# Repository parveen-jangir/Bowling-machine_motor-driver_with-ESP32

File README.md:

# Bowling-machine_motor-driver_with-ESP32
In this project we develop both hardware and software to control RPM of two 12v 10A motors using PWM generated by ESP32 developer board, we also control this hardware using mobile application via bluetooth and this all system deployed in a bowling machine.

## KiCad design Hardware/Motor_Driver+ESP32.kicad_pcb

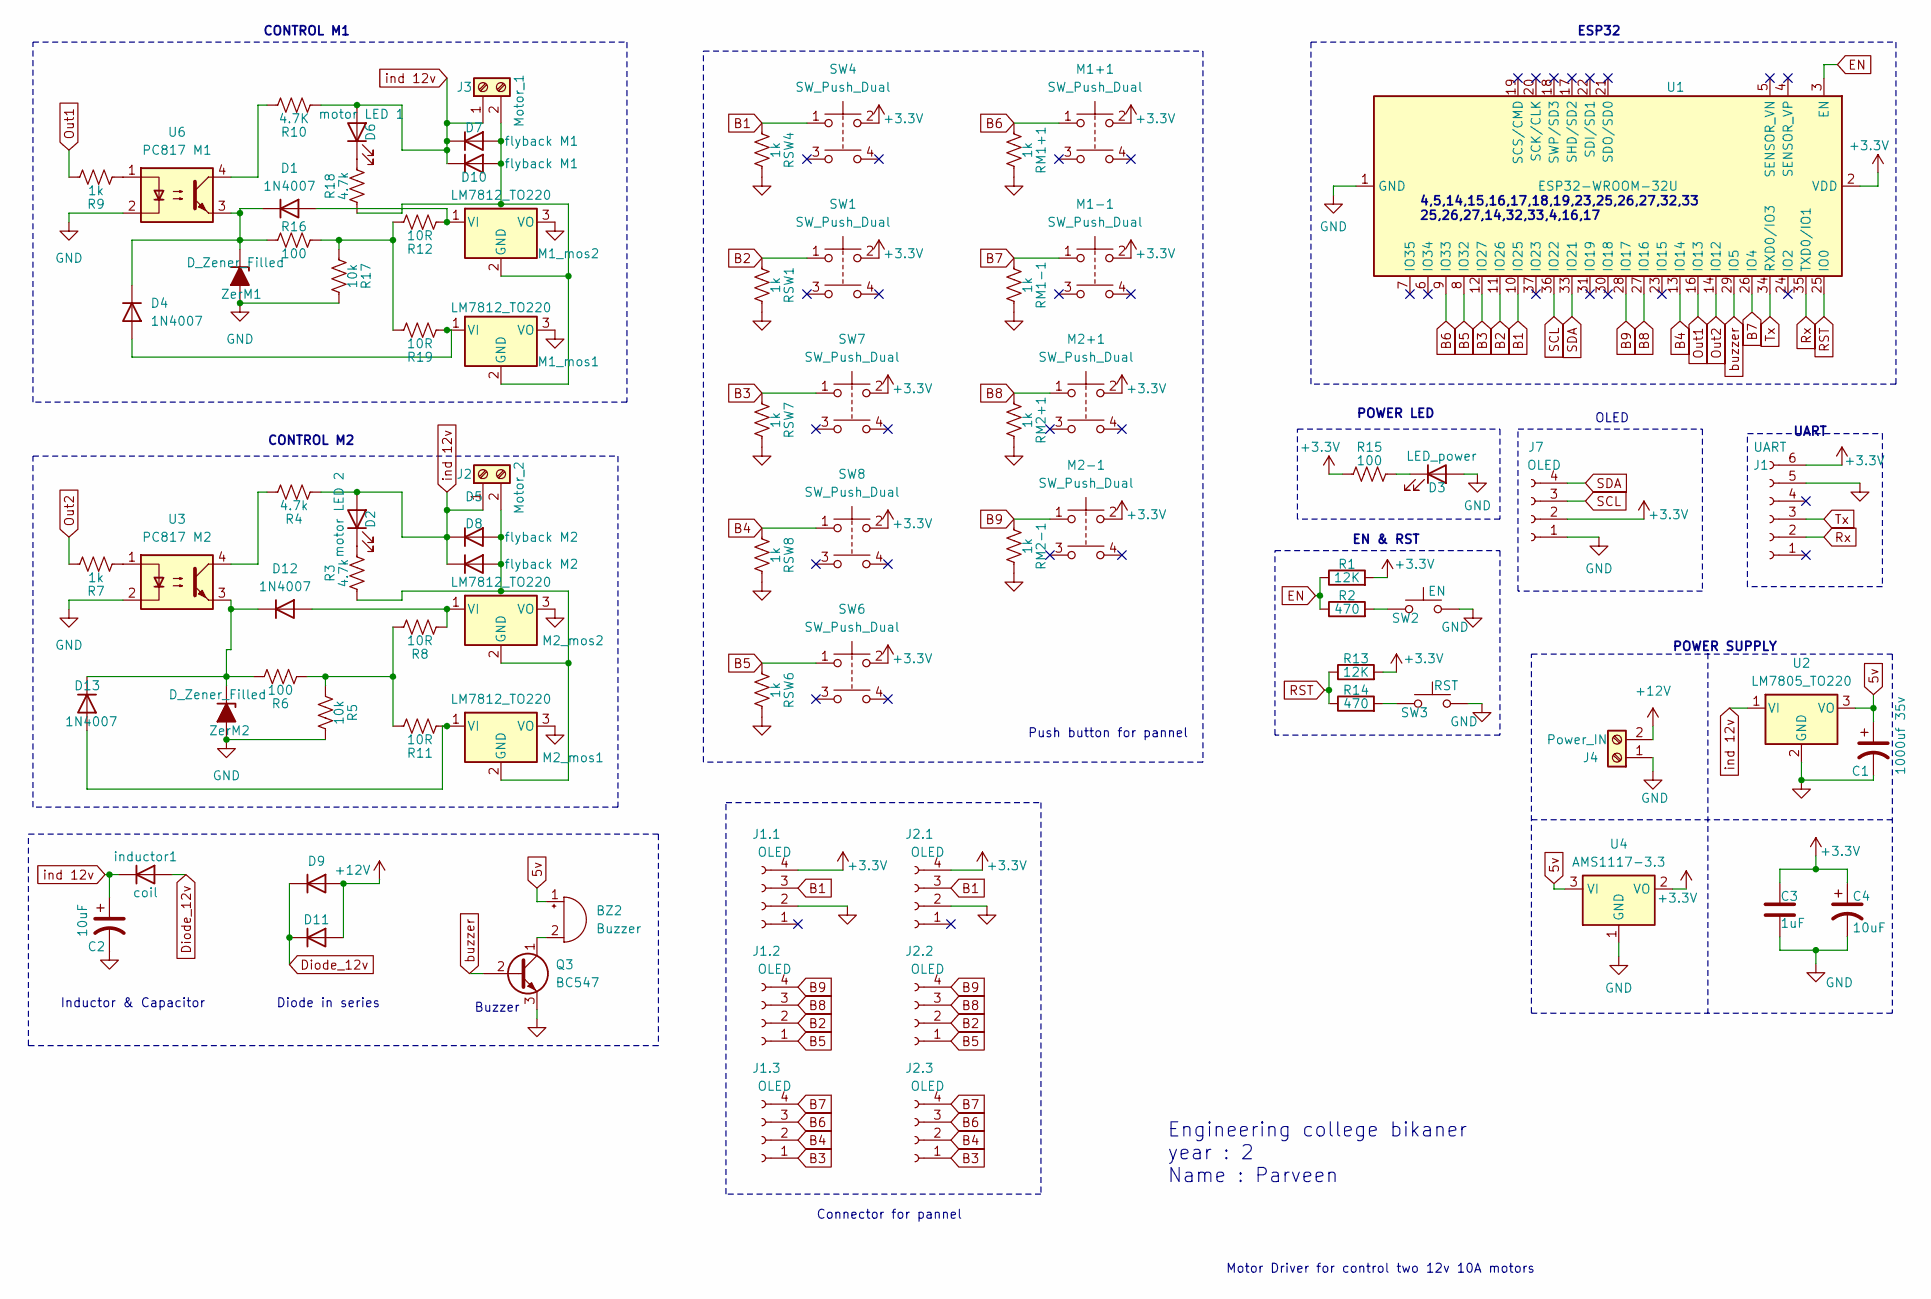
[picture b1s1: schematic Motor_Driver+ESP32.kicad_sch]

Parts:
BZ2: Buzzer; Buzzer_12x9.5RM7.6
C1: 1000uf 35v; C_Radial_D12.5mm_H20.0mm_P5.00mm
C2: 10uF; CP_Radial_D16.0mm_P7.50mm
C3: 1uF; C_Disc_D3.0mm_W2.0mm_P2.50mm
C4: 10uF; CP_Radial_D5.0mm_P2.50mm
D1, D4, D12, D13: 1N4007; D_DO-41_SOD81_P10.16mm_Horizontal
D2: motor LED 2; LED_0805_2012Metric_Pad1.15x1.40mm_HandSolder
D3: LED_power; LED_0805_2012Metric_Pad1.15x1.40mm_HandSolder
D5, D8, D9, D11: flyback M2; D_DO-201AD_P15.24mm_Horizontal
D6: motor LED 1; LED_0805_2012Metric_Pad1.15x1.40mm_HandSolder
D7, D10: flyback M1; D_DO-201AD_P15.24mm_Horizontal
J1: UART; PinHeader_1x06_P2.54mm_Vertical
J1.1, J1.2, J1.3, J2.1, J2.2, J2.3, J7: OLED; PinHeader_1x04_P2.54mm_Vertical
J2: Motor_2; TerminalBlock_Altech_AK300-2_P5.00mm
J3: Motor_1; TerminalBlock_Altech_AK300-2_P5.00mm
J4: Power_IN; TerminalBlock_Altech_AK300-2_P5.00mm
M1+1, M1-1, M2+1, M2-1: SW_Push_Dual; SW_PUSH_6mm_H4.3mm
M1_mos1, M1_mos2, M2_mos1, M2_mos2: LM7812_TO220; TO-220-3_Vertical
Q3: BC547; TO-92_Inline
R1, R13: 12K; R_0805_2012Metric_Pad1.20x1.40mm_HandSolder
R2, R14: 470; R_0805_2012Metric_Pad1.20x1.40mm_HandSolder
R3, R4, R18: 4.7k; R_0805_2012Metric_Pad1.20x1.40mm_HandSolder
R5, R17: 10k; R_0805_2012Metric_Pad1.20x1.40mm_HandSolder
R6, R15, R16: 100; R_0805_2012Metric_Pad1.20x1.40mm_HandSolder
R7, R9: 1k; R_0805_2012Metric_Pad1.20x1.40mm_HandSolder
R8, R11, R12, R19: 10R; R_0805_2012Metric_Pad1.20x1.40mm_HandSolder
R10: 4.7K; R_0805_2012Metric_Pad1.20x1.40mm_HandSolder
RM1+1, RM1-1, RM2+1, RM2-1: 1k; R_0805_2012Metric_Pad1.20x1.40mm_HandSolder
RSW1, RSW4, RSW6, RSW7, RSW8: 1k; R_0805_2012Metric_Pad1.20x1.40mm_HandSolder
SW1, SW4, SW6, SW7, SW8: SW_Push_Dual; SW_PUSH_6mm_H4.3mm
SW2: EN; SW_Push_SPST_NO_Alps_SKRK
SW3: RST; SW_Push_SPST_NO_Alps_SKRK
U1: ESP32-WROOM-32U
U2: LM7805_TO220; TO-220-3_Vertical
U3: PC817 M2; DIP-4_W7.62mm
U4: AMS1117-3.3; SOT-223-3_TabPin2
U6: PC817 M1; DIP-4_W7.62mm
ZerM1, ZerM2: D_Zener_Filled; D_T-1_P10.16mm_Horizontal
inductor1: coil; D_DO-41_SOD81_P10.16mm_Horizontal

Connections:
5v: BZ2.1 (-), C1.1, U2.3 (VO), U4.3 (VI)
+3.3V: C3.1, C4.1, J1.6, J1.1.4, J2.1.4, J7.2, M1+1.2, M1-1.2, M2+1.2, M2-1.2, R1.2, R13.2, R15.1, SW1.2, SW4.2, SW6.2, SW7.2, SW8.2, U1.2 (VDD), U4.2 (VO)
+12V: D9.2 (A), D11.2 (A), J4.2
B1: J1.1.3, J2.1.3, RSW4.1, SW4.1, U1.10 (IO25)
B2: J1.2.2, J2.2.2, RSW1.1, SW1.1, U1.11 (IO26)
B3: J1.3.1, J2.3.1, RSW7.1, SW7.1, U1.12 (IO27)
B4: J1.3.2, J2.3.2, RSW8.1, SW8.1, U1.13 (IO14)
B5: J1.2.1, J2.2.1, RSW6.1, SW6.1, U1.8 (IO32)
B6: J1.3.3, J2.3.3, M1+1.1, RM1+1.1, U1.9 (IO33)
B7: J1.3.4, J2.3.4, M1-1.1, RM1-1.1, U1.26 (IO4)
B8: J1.2.3, J2.2.3, M2+1.1, RM2+1.1, U1.27 (IO16)
B9: J1.2.4, J2.2.4, M2-1.1, RM2-1.1, U1.28 (IO17)
Diode_12v: D9.1 (K), D11.1 (K), inductor1.2 (A)
EN: R1.1, R2.1, U1.3 (EN)
GND: C1.2, C2.2, C3.2, C4.2, D3.2 (A), J1.5, J1.1.2, J2.1.2, J4.1, J7.1, M1_mos1.3 (VO), M1_mos2.3 (VO), M2_mos1.3 (VO), M2_mos2.3 (VO), Q3.3 (E), R5.2, R17.2, RM1+1.2, RM1-1.2, RM2+1.2, RM2-1.2, RSW1.2, RSW4.2, RSW6.2, RSW7.2, RSW8.2, SW2.2, SW3.2, U1.1 (GND), U1.15 (GND), U1.38 (GND), U1.39 (GND), U2.2 (GND), U3.2, U4.1 (GND), U6.2, ZerM1.2 (A), ZerM2.2 (A)
unnamed: BZ2.2 (+), Q3.1 (C)
unnamed: D1.2 (A), M1_mos2.1 (VI), R12.1
unnamed: D1.1 (K), D4.1 (K), R16.2, U6.3, ZerM1.1 (K)
unnamed: D2.1 (K), R3.2
unnamed: D3.1 (K), R15.2
unnamed: D4.2 (A), M1_mos1.1 (VI), R19.1
unnamed: D5.2 (A), D8.2 (A), J2.2, M2_mos1.2 (GND), M2_mos2.2 (GND), R3.1
unnamed: D6.1 (K), R18.2
unnamed: D7.2 (A), D10.2 (A), J3.2, M1_mos1.2 (GND), M1_mos2.2 (GND), R18.1
unnamed: D12.2 (A), M2_mos2.1 (VI), R8.1
unnamed: D12.1 (K), D13.1 (K), R6.2, U3.3, ZerM2.1 (K)
unnamed: D13.2 (A), M2_mos1.1 (VI), R11.1
unnamed: R2.2, SW2.1
unnamed: R4.2, U3.4
unnamed: R7.1, U3.1
unnamed: R9.1, U6.1
unnamed: R10.2, U6.4
unnamed: R5.1, R6.1, R8.2, R11.2
unnamed: R12.2, R16.1, R17.1, R19.2
unnamed: R14.2, SW3.1
Out1: R9.2, U1.16 (IO13)
Out2: R7.2, U1.14 (IO12)
RST: R13.1, R14.1, U1.25 (IO0)
Rx: J1.2, U1.35 (TXD0/IO1)
SCL: J7.3, U1.36 (IO22)
SDA: J7.4, U1.33 (IO21)
Tx: J1.3, U1.34 (RXD0/IO3)
buzzer: Q3.2 (B), U1.29 (IO5)
ind 12v: C2.1, D2.2 (A), D5.1 (K), D6.2 (A), D7.1 (K), D8.1 (K), D10.1 (K), J2.1, J3.1, R4.1, R10.1, U2.1 (VI), inductor1.1 (K)

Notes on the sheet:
OLED
Push button for pannel
4,5,14,15,16,17,18,19,23,25,26,27,32,33 25,26,27,14,32,33,4,16,17
Connector for pannel
EN & RST
UART
Buzzer
CONTROL M2
CONTROL M1
Inductor & Capacitor
Engineering college bikaner year : 2 Name : Parveen
POWER SUPPLY
Diode in series
POWER LED
Motor Driver for control two 12v 10A motors
ESP32

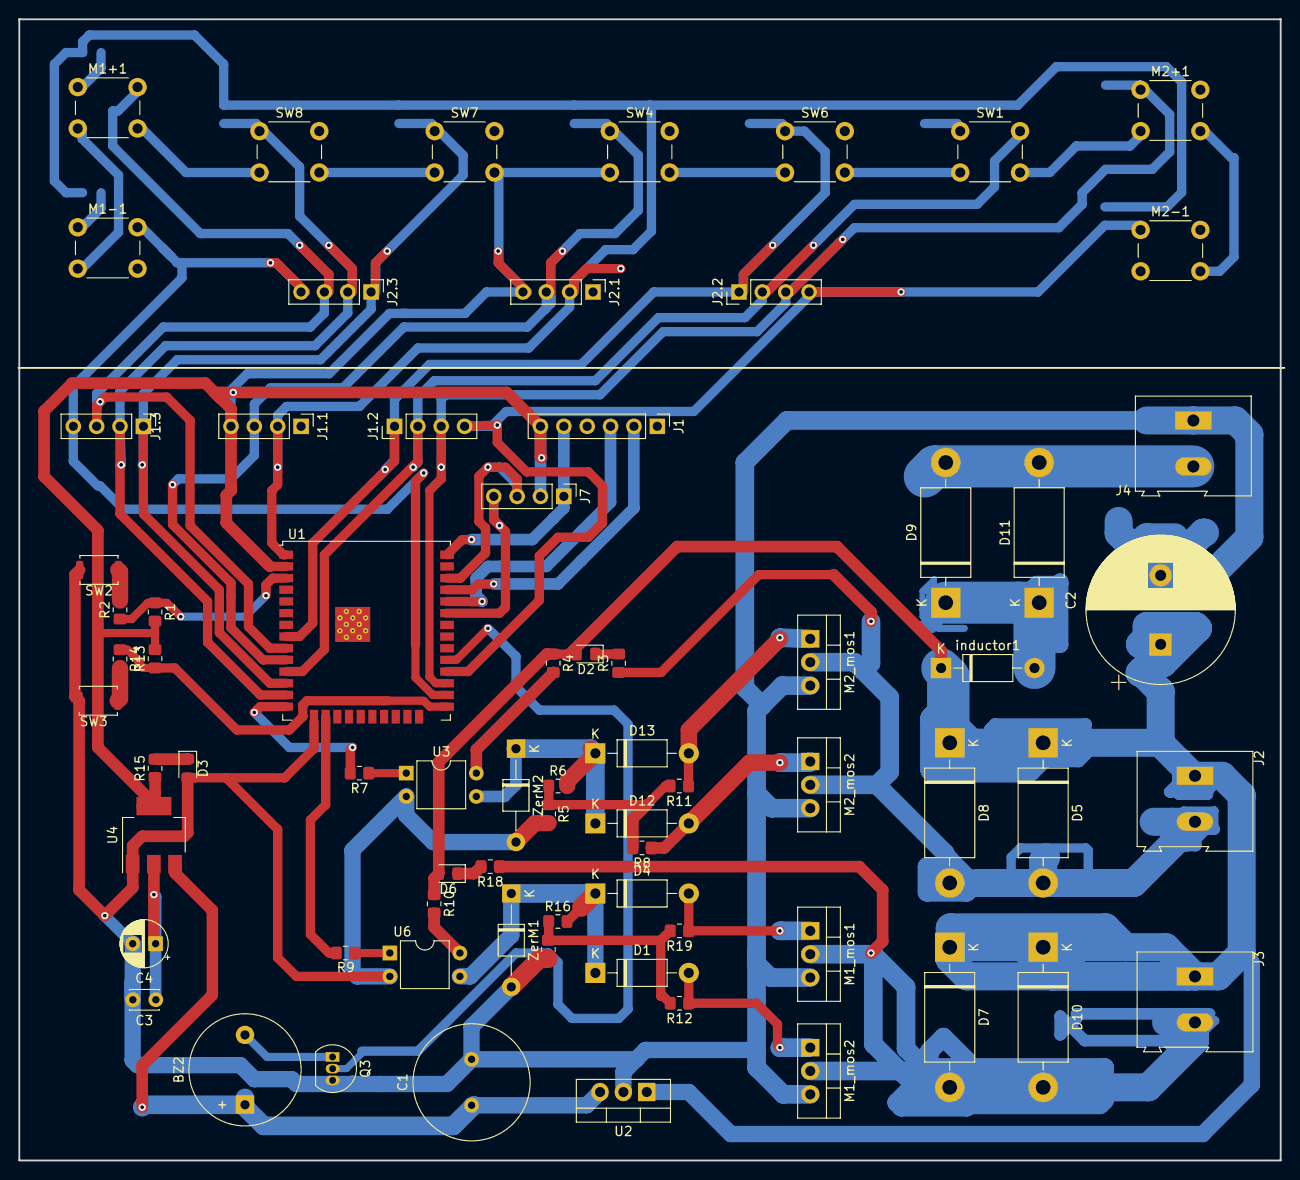
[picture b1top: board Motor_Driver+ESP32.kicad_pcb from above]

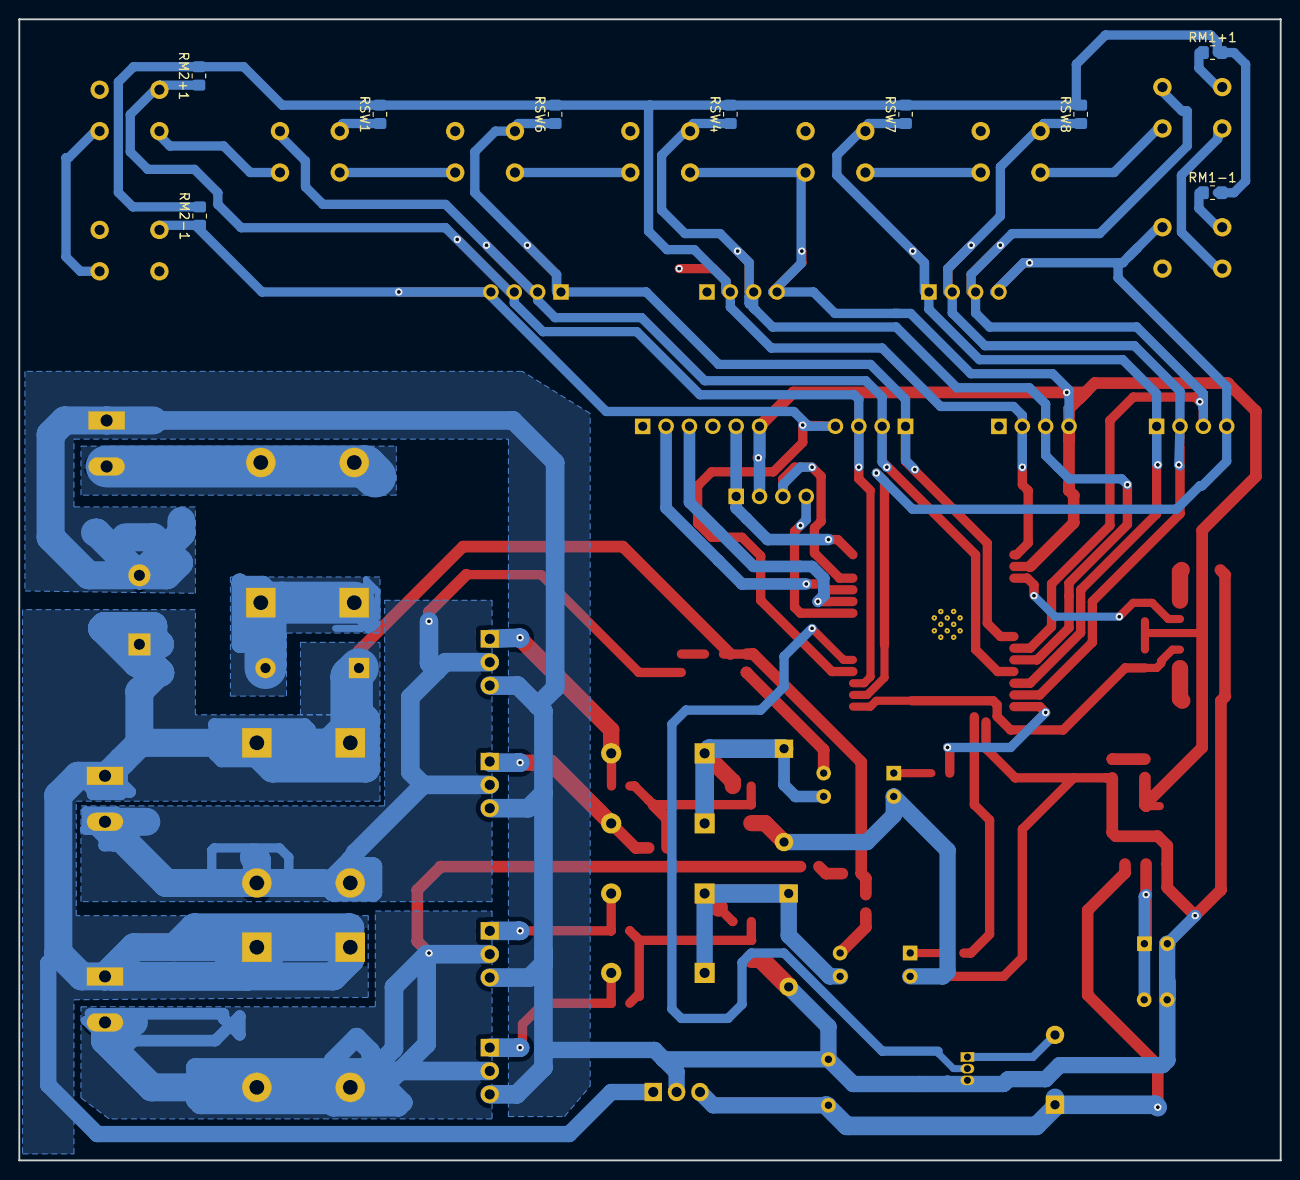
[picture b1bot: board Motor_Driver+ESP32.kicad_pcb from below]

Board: 2 copper layers, 137.2 x 124.1 mm, 81 parts (9 on the bottom side), 44 nets.

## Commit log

2023-12-30 This is software part of our project
2023-12-30 assign '\0' instead of NULL to btdata
2023-12-30 Hardware part of this project
2024-03-26 We complete the first stage of ball Feeder
2024-03-26 Add OVER THE AIR in ball feeder
2024-03-29 Ball Feeder stage two is complete
